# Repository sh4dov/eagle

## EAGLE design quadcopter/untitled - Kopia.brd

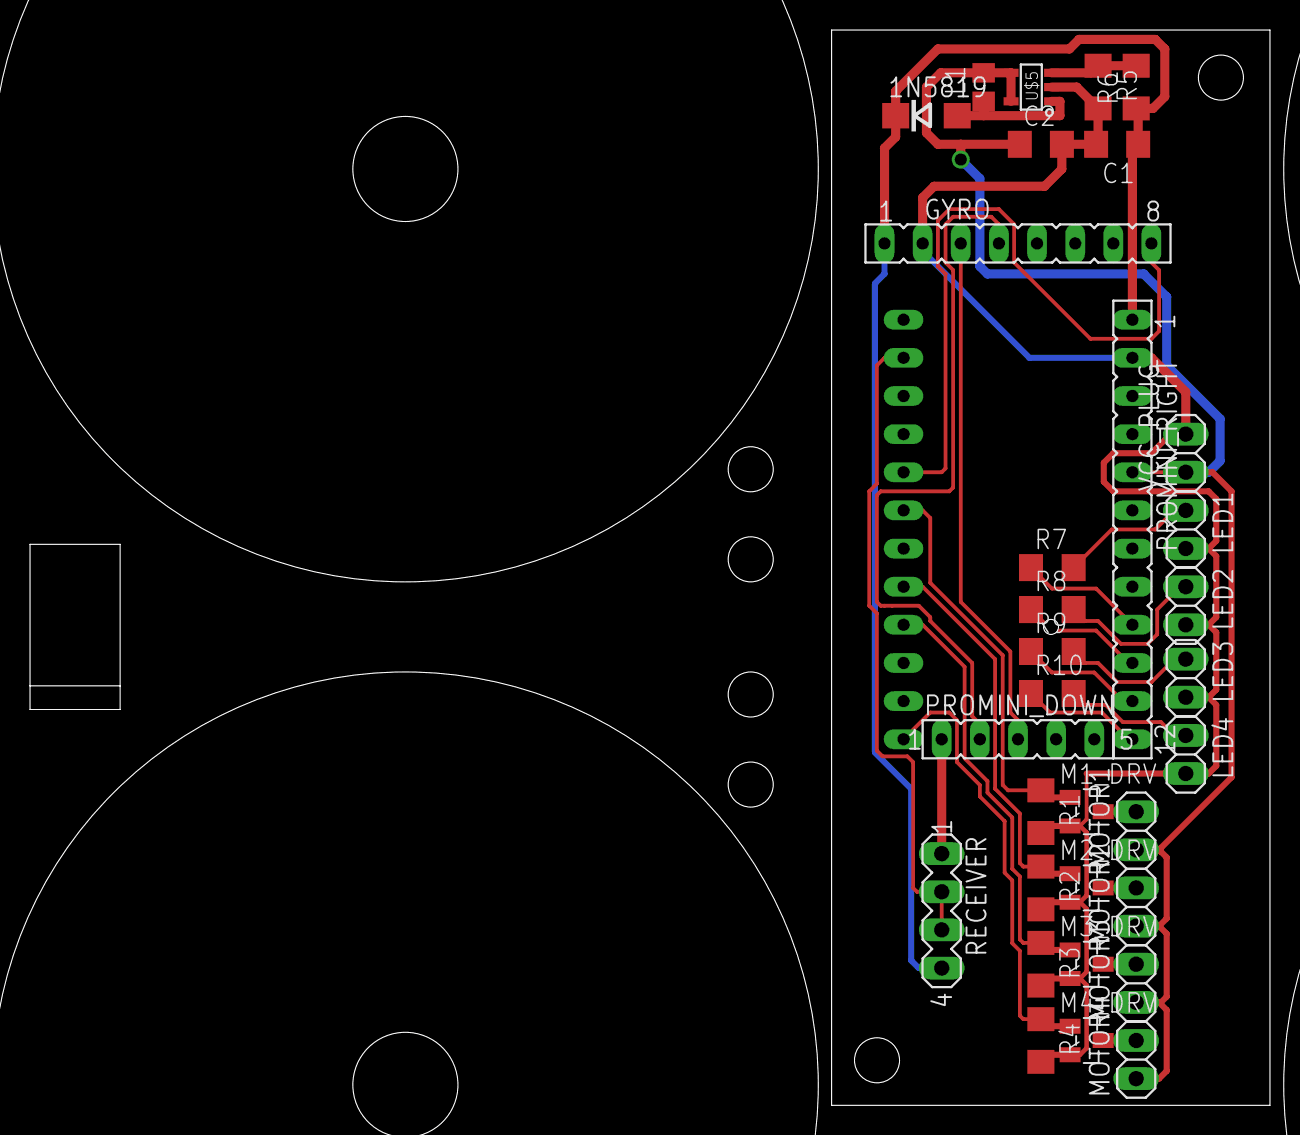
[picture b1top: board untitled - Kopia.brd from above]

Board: 2 copper layers, 29.2 x 71.6 mm, 33 parts (1 on the bottom side), 26 nets.

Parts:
1N5819: DO214AC
C1, C2: 1uF; C1206
GYRO: FE08
L1: 10uH; R0805
LED1, LED2, LED3, LED4: 1X02
M1_DRV, M2_DRV, M3_DRV, M4_DRV: AO3400A; SOT-23
MOTOR1, MOTOR2, MOTOR3, MOTOR4: 1X02
PROMINI_DOWN: FE05-1
PROMINI_LEFT: FE12
PROMINI_RIGHT: FE12
R1, R2, R3, R4, R5: 1k; R1206
R6: 3k; R1206
R7, R8, R9, R10: 220; R1206
RECEIVER: MA04-1
U$5: SOT-23-5
VCC_PLUG: 1X02

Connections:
10: PROMINI_RIGHT.12, R10.1
11: PROMINI_RIGHT.11, R9.1
12: PROMINI_RIGHT.10, R8.1
13: PROMINI_RIGHT.9, R7.1
+5V: 1N5819.C, C1.1, GYRO.1, PROMINI_RIGHT.1, R6.1, RECEIVER.4
GND: C1.2, C2.2, GYRO.2, LED1.2, LED2.2, LED3.2, LED4.2, M1_DRV.2, M2_DRV.2, M3_DRV.2, M4_DRV.2, PROMINI_RIGHT.2, R1.2, R2.2, R3.2, R4.2, R5.2, U$5.2, VCC_PLUG.2
INT: GYRO.8, PROMINI_LEFT.5
M1_IN: M1_DRV.1, PROMINI_LEFT.6, R1.1
M1_OUT: M1_DRV.3, MOTOR1.2
M2_IN: M2_DRV.1, PROMINI_LEFT.8, R2.1
M2_OUT: M2_DRV.3, MOTOR2.2
M3_IN: M3_DRV.1, PROMINI_LEFT.9, R3.1
M3_OUT: M3_DRV.3, MOTOR3.2
M4_IN: M4_DRV.1, PROMINI_LEFT.12, R4.1
M4_OUT: M4_DRV.3, MOTOR4.2
unnamed: LED4.1, R10.2
unnamed: 1N5819.A, L1.1, U$5.1
unnamed: R5.1, R6.2, U$5.3
unnamed: LED3.1, R9.2
unnamed: LED2.1, R8.2
unnamed: LED1.1, R7.2
RECEIVER_GND: PROMINI_DOWN.1, RECEIVER.1
RX: PROMINI_LEFT.2, RECEIVER.2, RECEIVER.3
SCL: GYRO.3, PROMINI_DOWN.3
SDA: GYRO.4, PROMINI_DOWN.2
VCC: C2.1, L1.2, MOTOR1.1, MOTOR2.1, MOTOR3.1, MOTOR4.1, PROMINI_RIGHT.5, U$5.4, U$5.5, VCC_PLUG.1

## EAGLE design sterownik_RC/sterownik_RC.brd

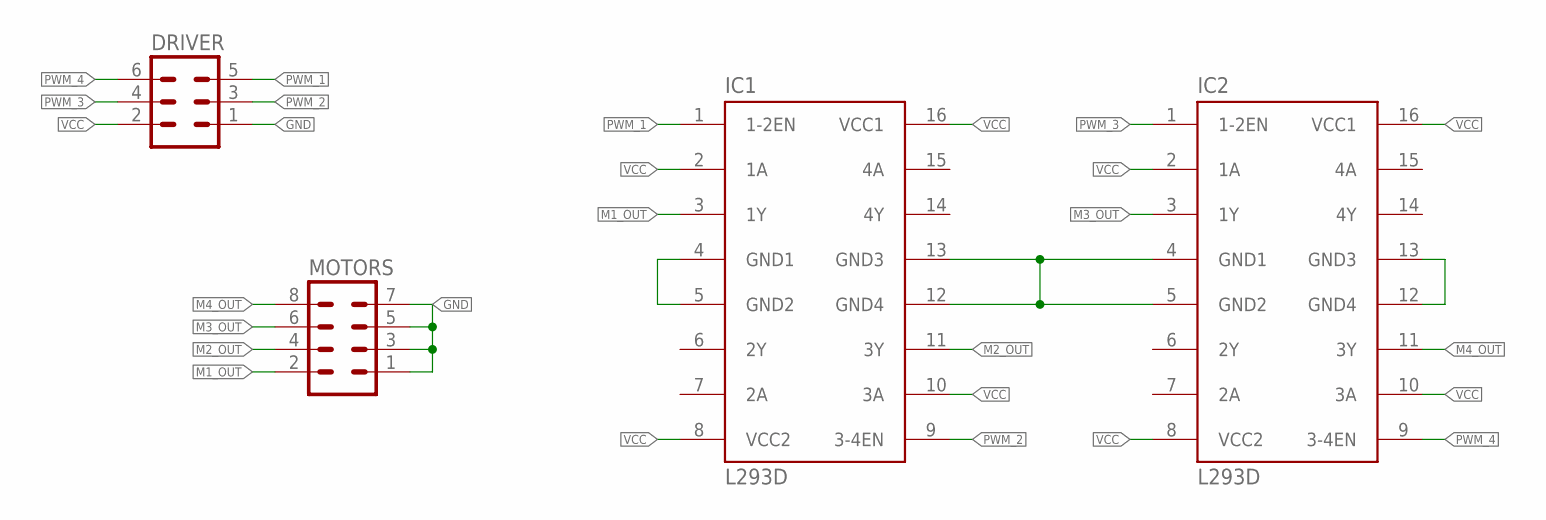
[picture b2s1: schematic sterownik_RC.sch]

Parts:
DRIVER: MA03-2
IC1, IC2: L293D; DIL16
MOTORS: MA04-2

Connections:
GND: DRIVER.1, IC1.4 (GND1), IC1.5 (GND2), IC1.12 (GND4), IC1.13 (GND3), IC2.4 (GND1), IC2.5 (GND2), IC2.12 (GND4), IC2.13 (GND3), MOTORS.1, MOTORS.3, MOTORS.5, MOTORS.7
M1_OUT: IC1.3 (1Y), MOTORS.2
M2_OUT: IC1.11 (3Y), MOTORS.4
M3_OUT: IC2.3 (1Y), MOTORS.6
M4_OUT: IC2.11 (3Y), MOTORS.8
PWM_1: DRIVER.5, IC1.1 (1-2EN)
PWM_2: DRIVER.3, IC1.9 (3-4EN)
PWM_3: DRIVER.4, IC2.1 (1-2EN)
PWM_4: DRIVER.6, IC2.9 (3-4EN)
VCC: DRIVER.2, IC1.2 (1A), IC1.8 (VCC2), IC1.10 (3A), IC1.16 (VCC1), IC2.2 (1A), IC2.8 (VCC2), IC2.10 (3A), IC2.16 (VCC1)

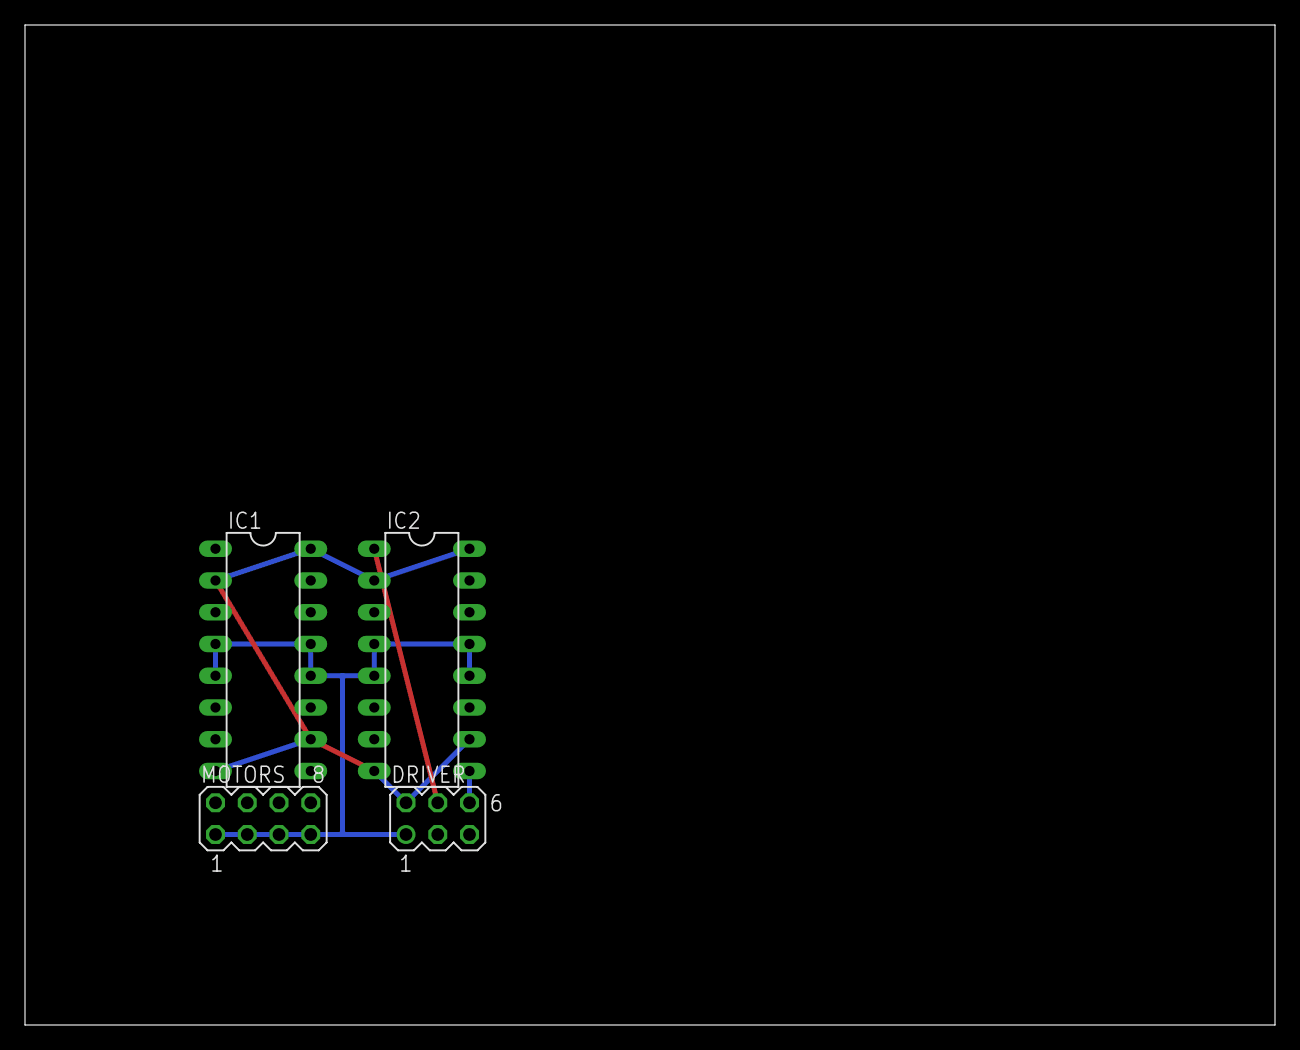
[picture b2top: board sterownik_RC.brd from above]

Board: 2 copper layers, 100.0 x 80.0 mm, 4 parts (0 on the bottom side), 10 nets.

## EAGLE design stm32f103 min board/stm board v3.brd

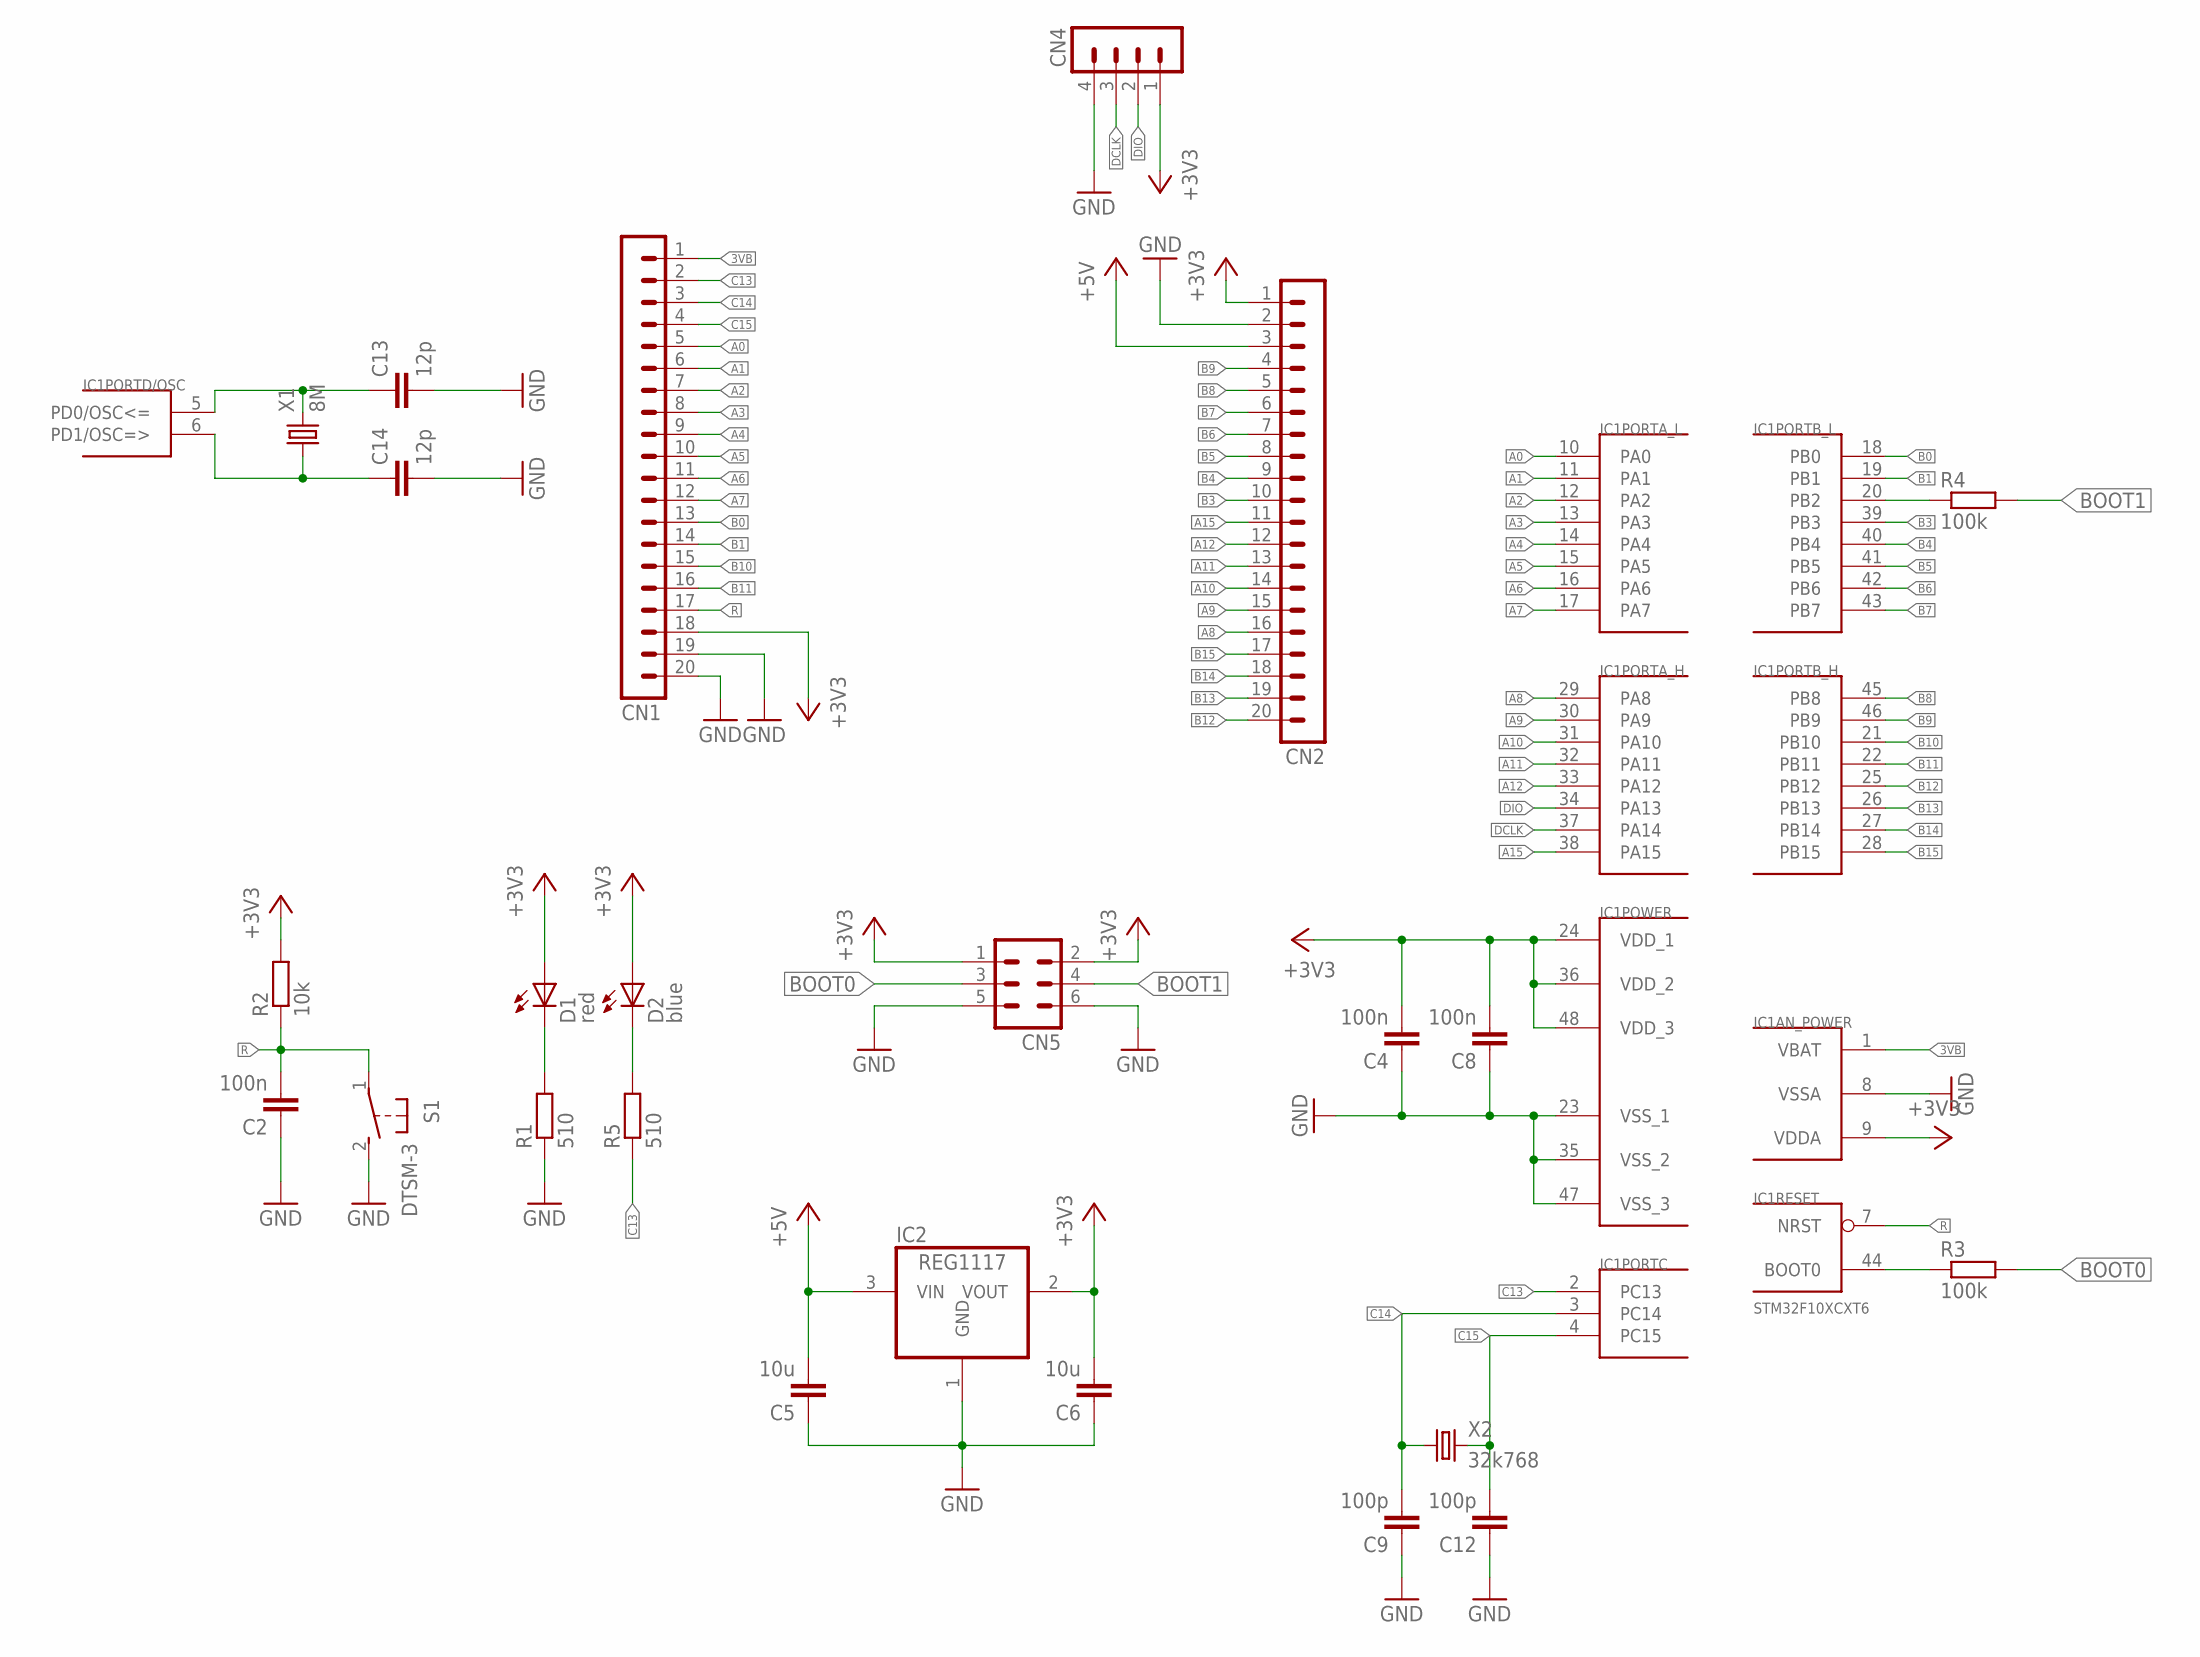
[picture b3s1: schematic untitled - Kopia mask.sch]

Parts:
C2, C4, C8: 100n; C0805K
C5, C6: 10u; C0805K
C9, C12: 100p; C0805K
C13, C14: 12p; C0805K
CN1, CN2: MA20-1L
CN4: MA04-1
CN5: MA03-2
D1: red; SML0805
D2: blue; SML0805
IC1: STM32F10XCXT6; TQFP48
IC2: REG1117; SOT223
R1, R5: 510; M0805
R2: 10k; R1206
R3, R4: 100k; M0805
S1: DTSM-3
X1: 8M; HC49/S
X2: 32k768; TC26H

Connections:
3VB: CN1.1, IC1.1 (VBAT)
+3V3: C4.2, C6.2, C8.2, CN1.18, CN2.1, CN4.1, CN5.1, CN5.2, D1.A, D2.A, IC1.9 (VDDA), IC1.24 (VDD_1), IC1.36 (VDD_2), IC1.48 (VDD_3), IC2.2 (VOUT), R2.2
+5V: C5.2, CN2.3, IC2.3 (VIN)
A0: CN1.5, IC1.10 (PA0)
A1: CN1.6, IC1.11 (PA1)
A2: CN1.7, IC1.12 (PA2)
A3: CN1.8, IC1.13 (PA3)
A4: CN1.9, IC1.14 (PA4)
A5: CN1.10, IC1.15 (PA5)
A6: CN1.11, IC1.16 (PA6)
A7: CN1.12, IC1.17 (PA7)
A8: CN2.16, IC1.29 (PA8)
A9: CN2.15, IC1.30 (PA9)
A10: CN2.14, IC1.31 (PA10)
A11: CN2.13, IC1.32 (PA11)
A12: CN2.12, IC1.33 (PA12)
A15: CN2.11, IC1.38 (PA15)
B0: CN1.13, IC1.18 (PB0)
B1: CN1.14, IC1.19 (PB1)
B3: CN2.10, IC1.39 (PB3)
B4: CN2.9, IC1.40 (PB4)
B5: CN2.8, IC1.41 (PB5)
B6: CN2.7, IC1.42 (PB6)
B7: CN2.6, IC1.43 (PB7)
B8: CN2.5, IC1.45 (PB8)
B9: CN2.4, IC1.46 (PB9)
B10: CN1.15, IC1.21 (PB10)
B11: CN1.16, IC1.22 (PB11)
B12: CN2.20, IC1.25 (PB12)
B13: CN2.19, IC1.26 (PB13)
B14: CN2.18, IC1.27 (PB14)
B15: CN2.17, IC1.28 (PB15)
BOOT0: CN5.3, R3.2
BOOT1: CN5.4, R4.2
C13: CN1.2, IC1.2 (PC13), R5.1
C14: C9.2, CN1.3, IC1.3 (PC14), X2.1
C15: C12.2, CN1.4, IC1.4 (PC15), X2.2
DCLK: CN4.3, IC1.37 (PA14)
DIO: CN4.2, IC1.34 (PA13)
GND: C2.1, C4.1, C5.1, C6.1, C8.1, C9.1, C12.1, C13.2, C14.2, CN1.19, CN1.20, CN2.2, CN4.4, CN5.5, CN5.6, IC1.8 (VSSA), IC1.23 (VSS_1), IC1.35 (VSS_2), IC1.47 (VSS_3), IC2.1 (GND), R1.1, S1.2
unnamed: C13.1, IC1.5 (PD0/OSC<=), X1.2
unnamed: C14.1, IC1.6 (PD1/OSC=>), X1.1
unnamed: D1.C, R1.2
unnamed: D2.C, R5.2
R: C2.2, CN1.17, IC1.7 (NRST), R2.1, S1.1
_BOOT0: IC1.44 (BOOT0), R3.1
_BOOT1: IC1.20 (PB2), R4.1

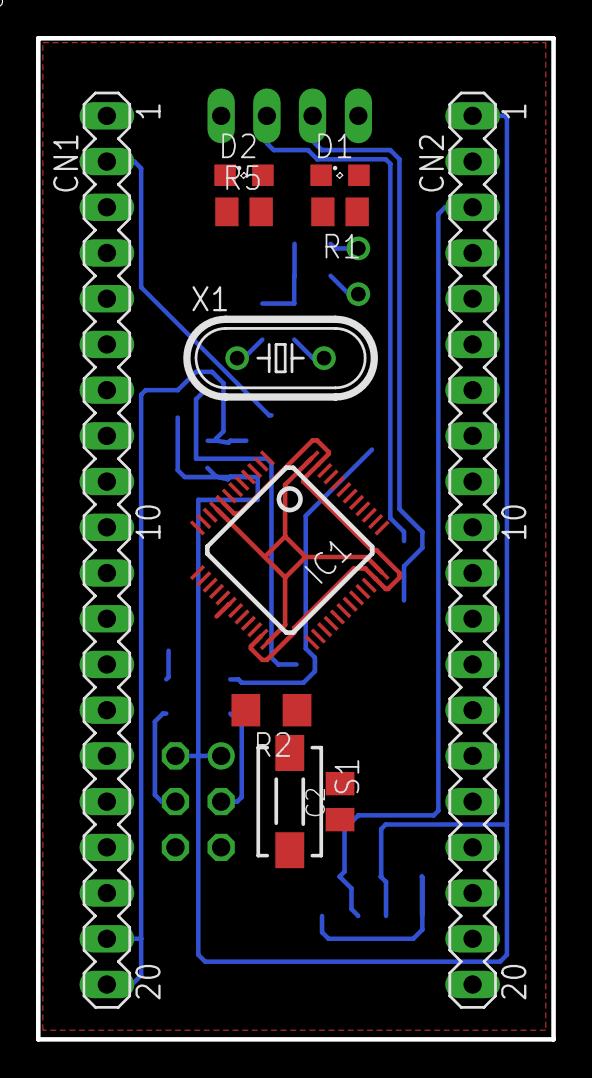
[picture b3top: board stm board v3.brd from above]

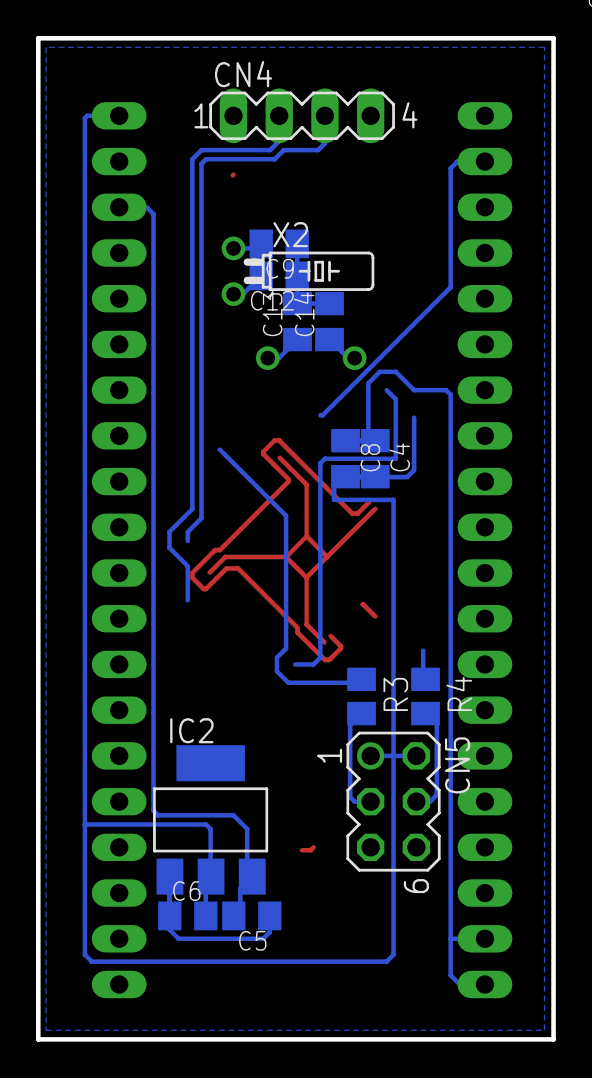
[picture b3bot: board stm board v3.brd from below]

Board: 2 copper layers, 28.6 x 55.6 mm, 25 parts (14 on the bottom side), 47 nets.
